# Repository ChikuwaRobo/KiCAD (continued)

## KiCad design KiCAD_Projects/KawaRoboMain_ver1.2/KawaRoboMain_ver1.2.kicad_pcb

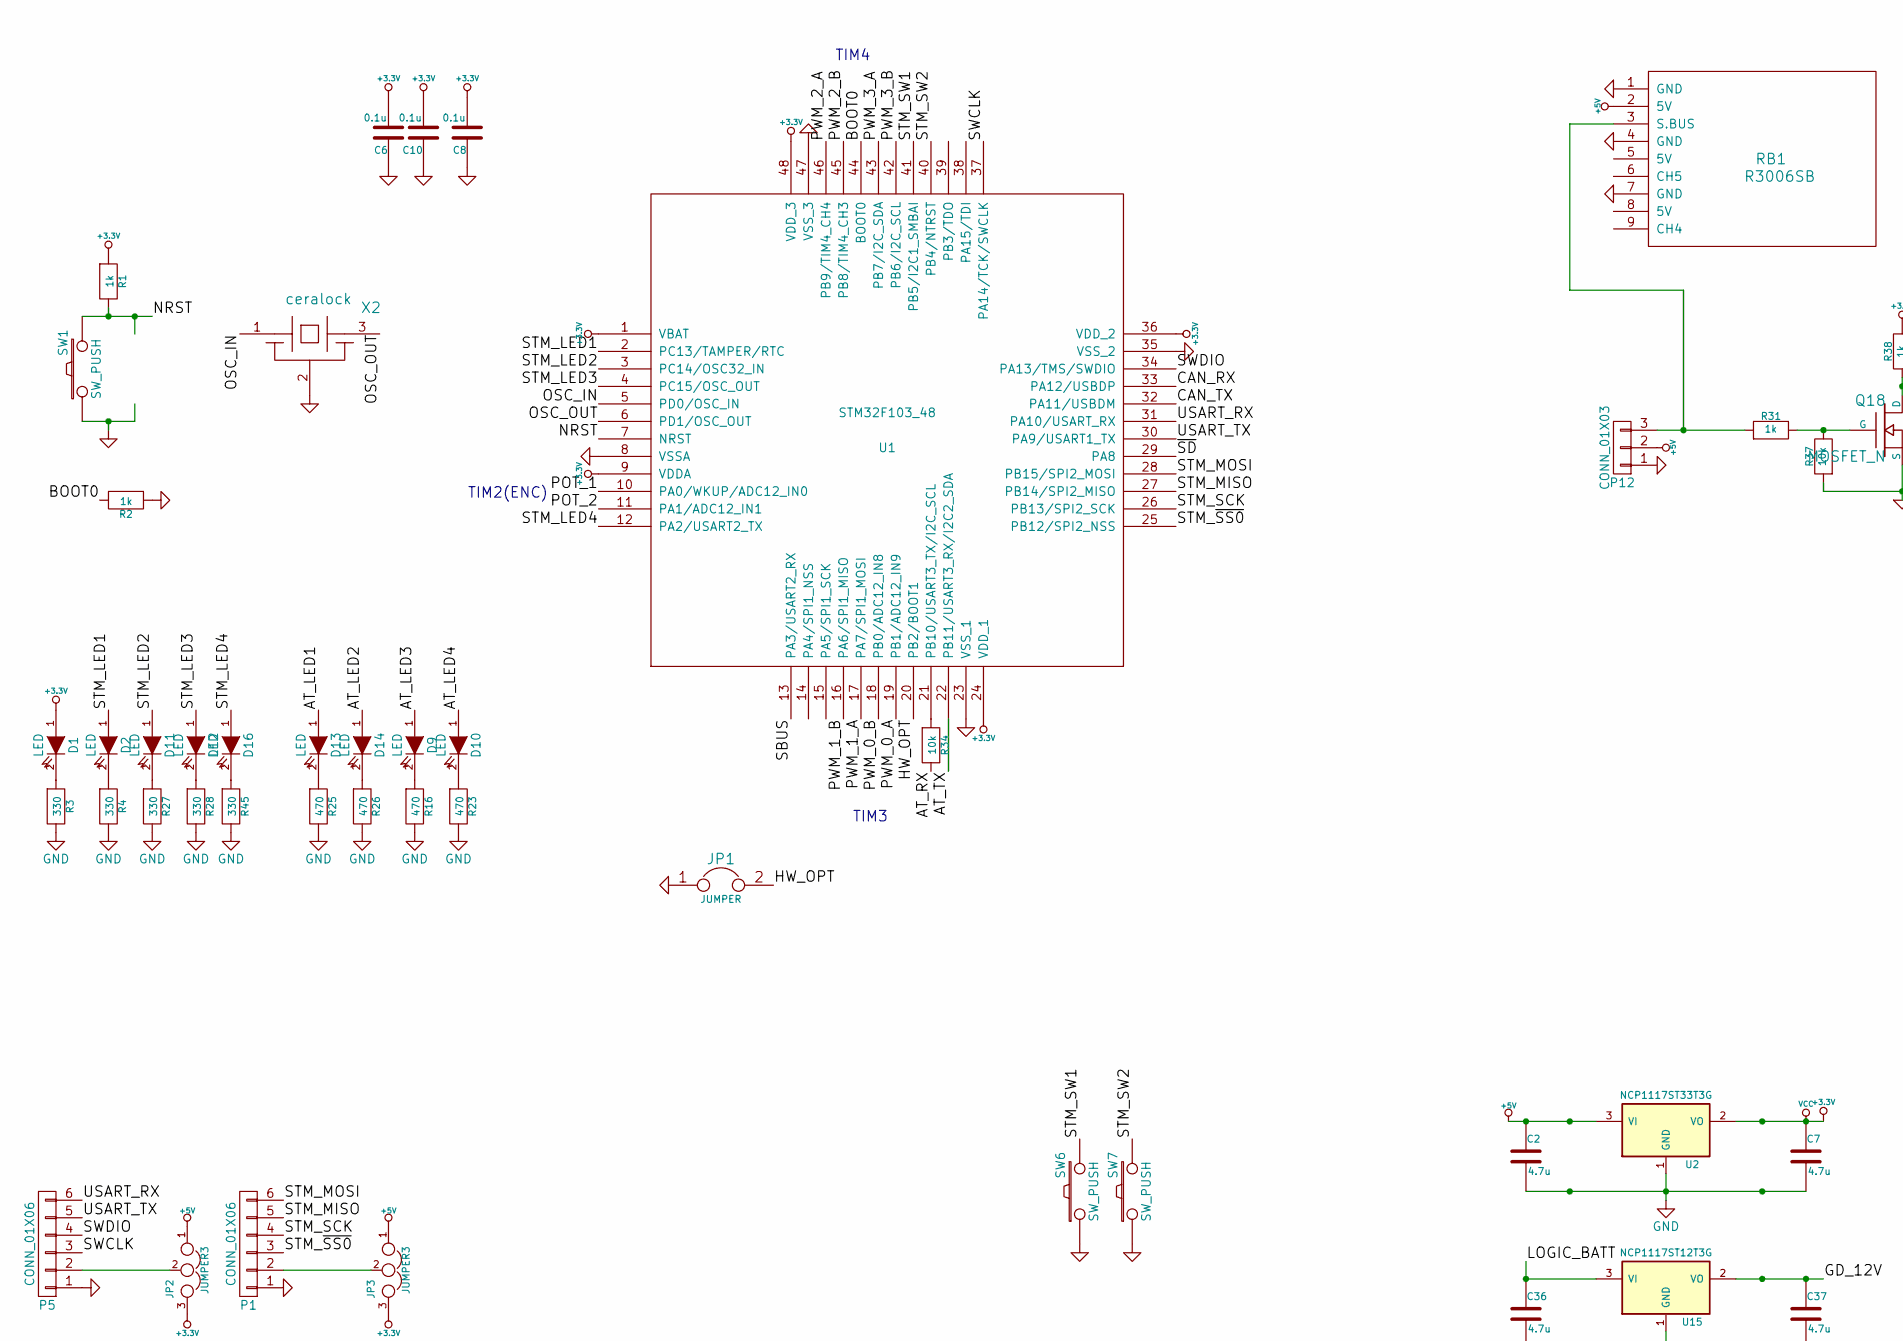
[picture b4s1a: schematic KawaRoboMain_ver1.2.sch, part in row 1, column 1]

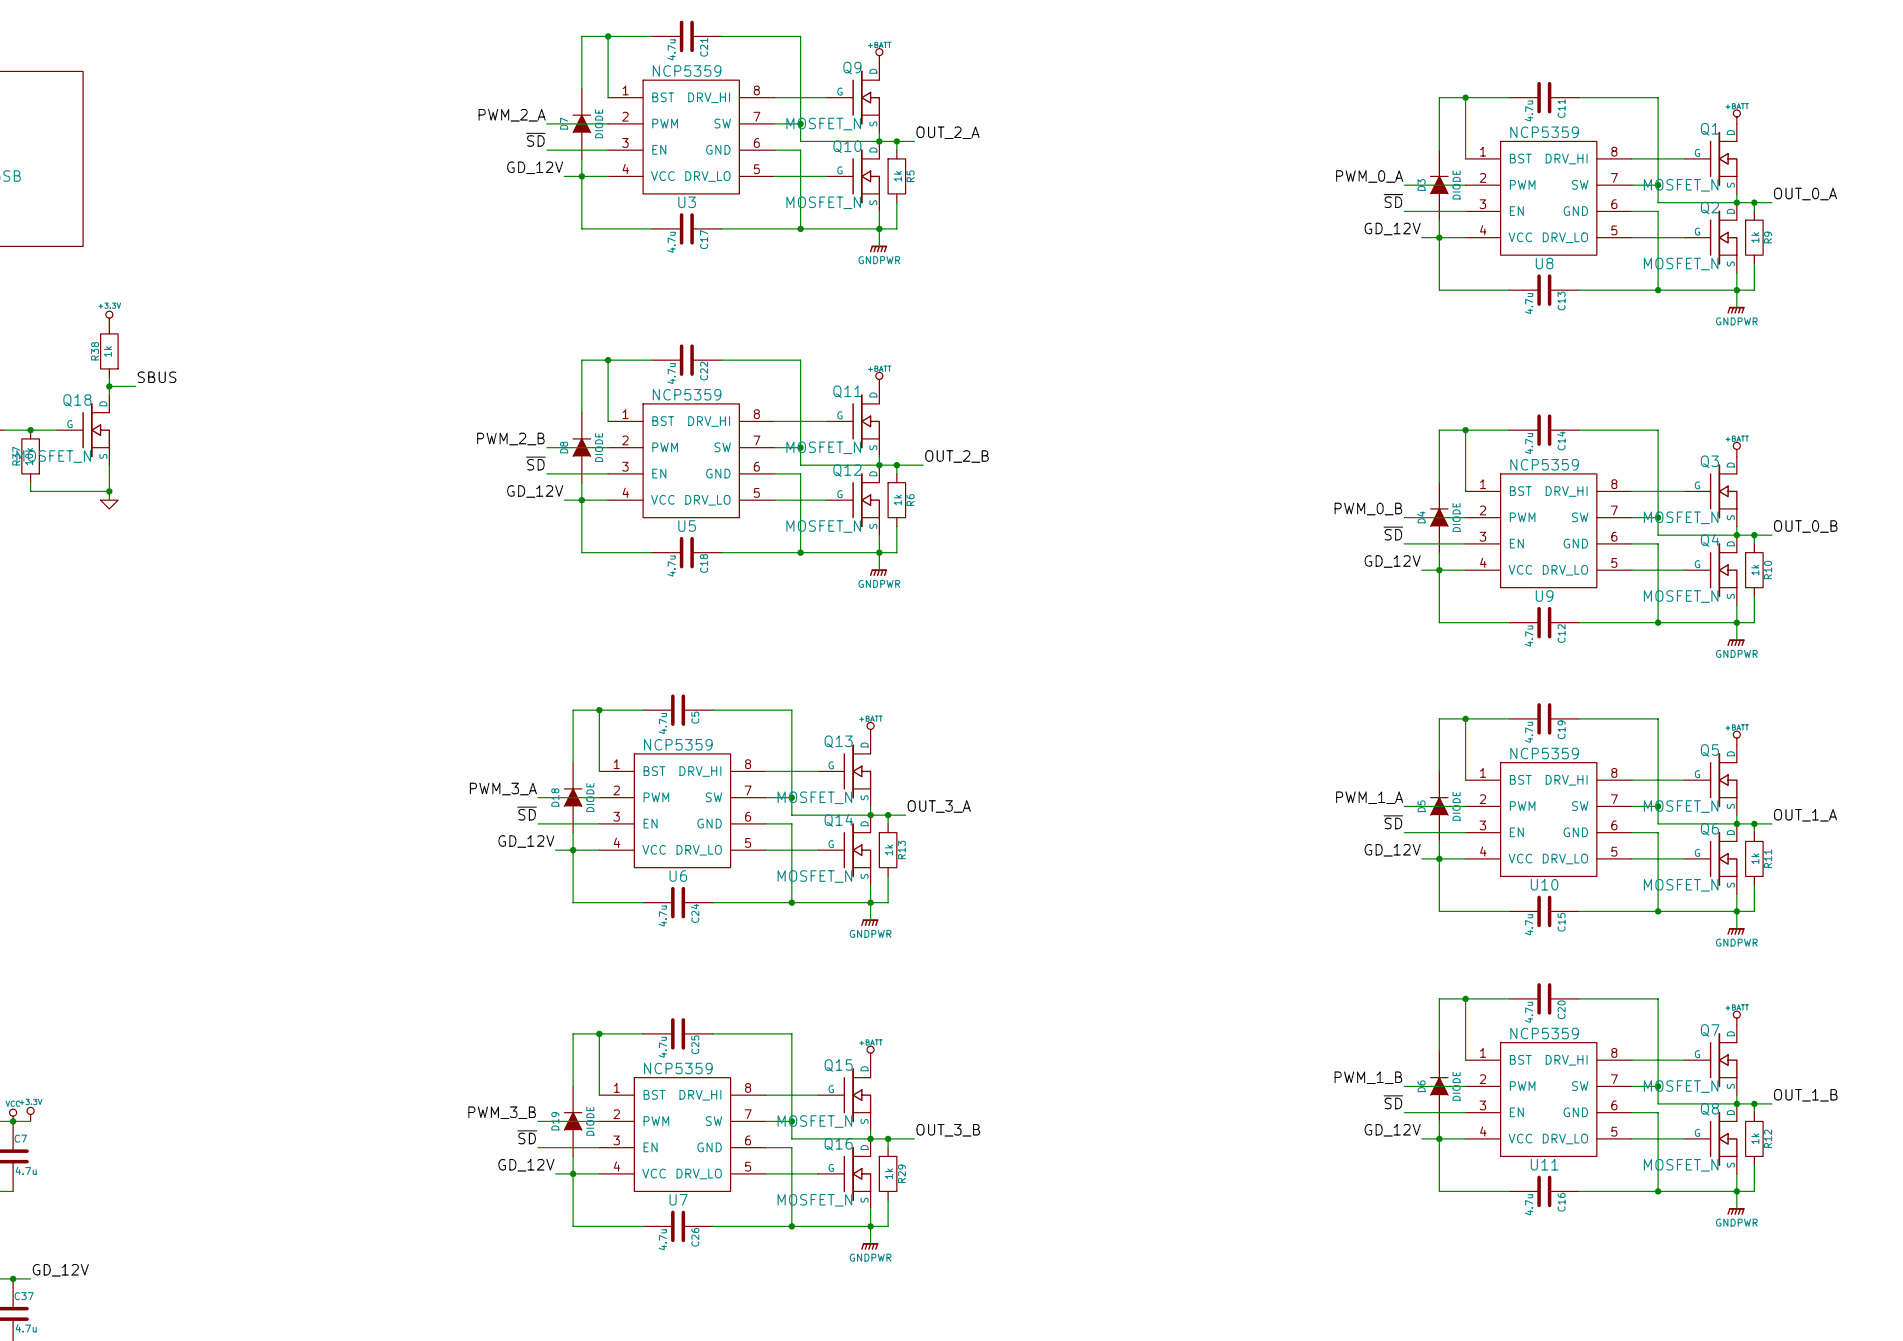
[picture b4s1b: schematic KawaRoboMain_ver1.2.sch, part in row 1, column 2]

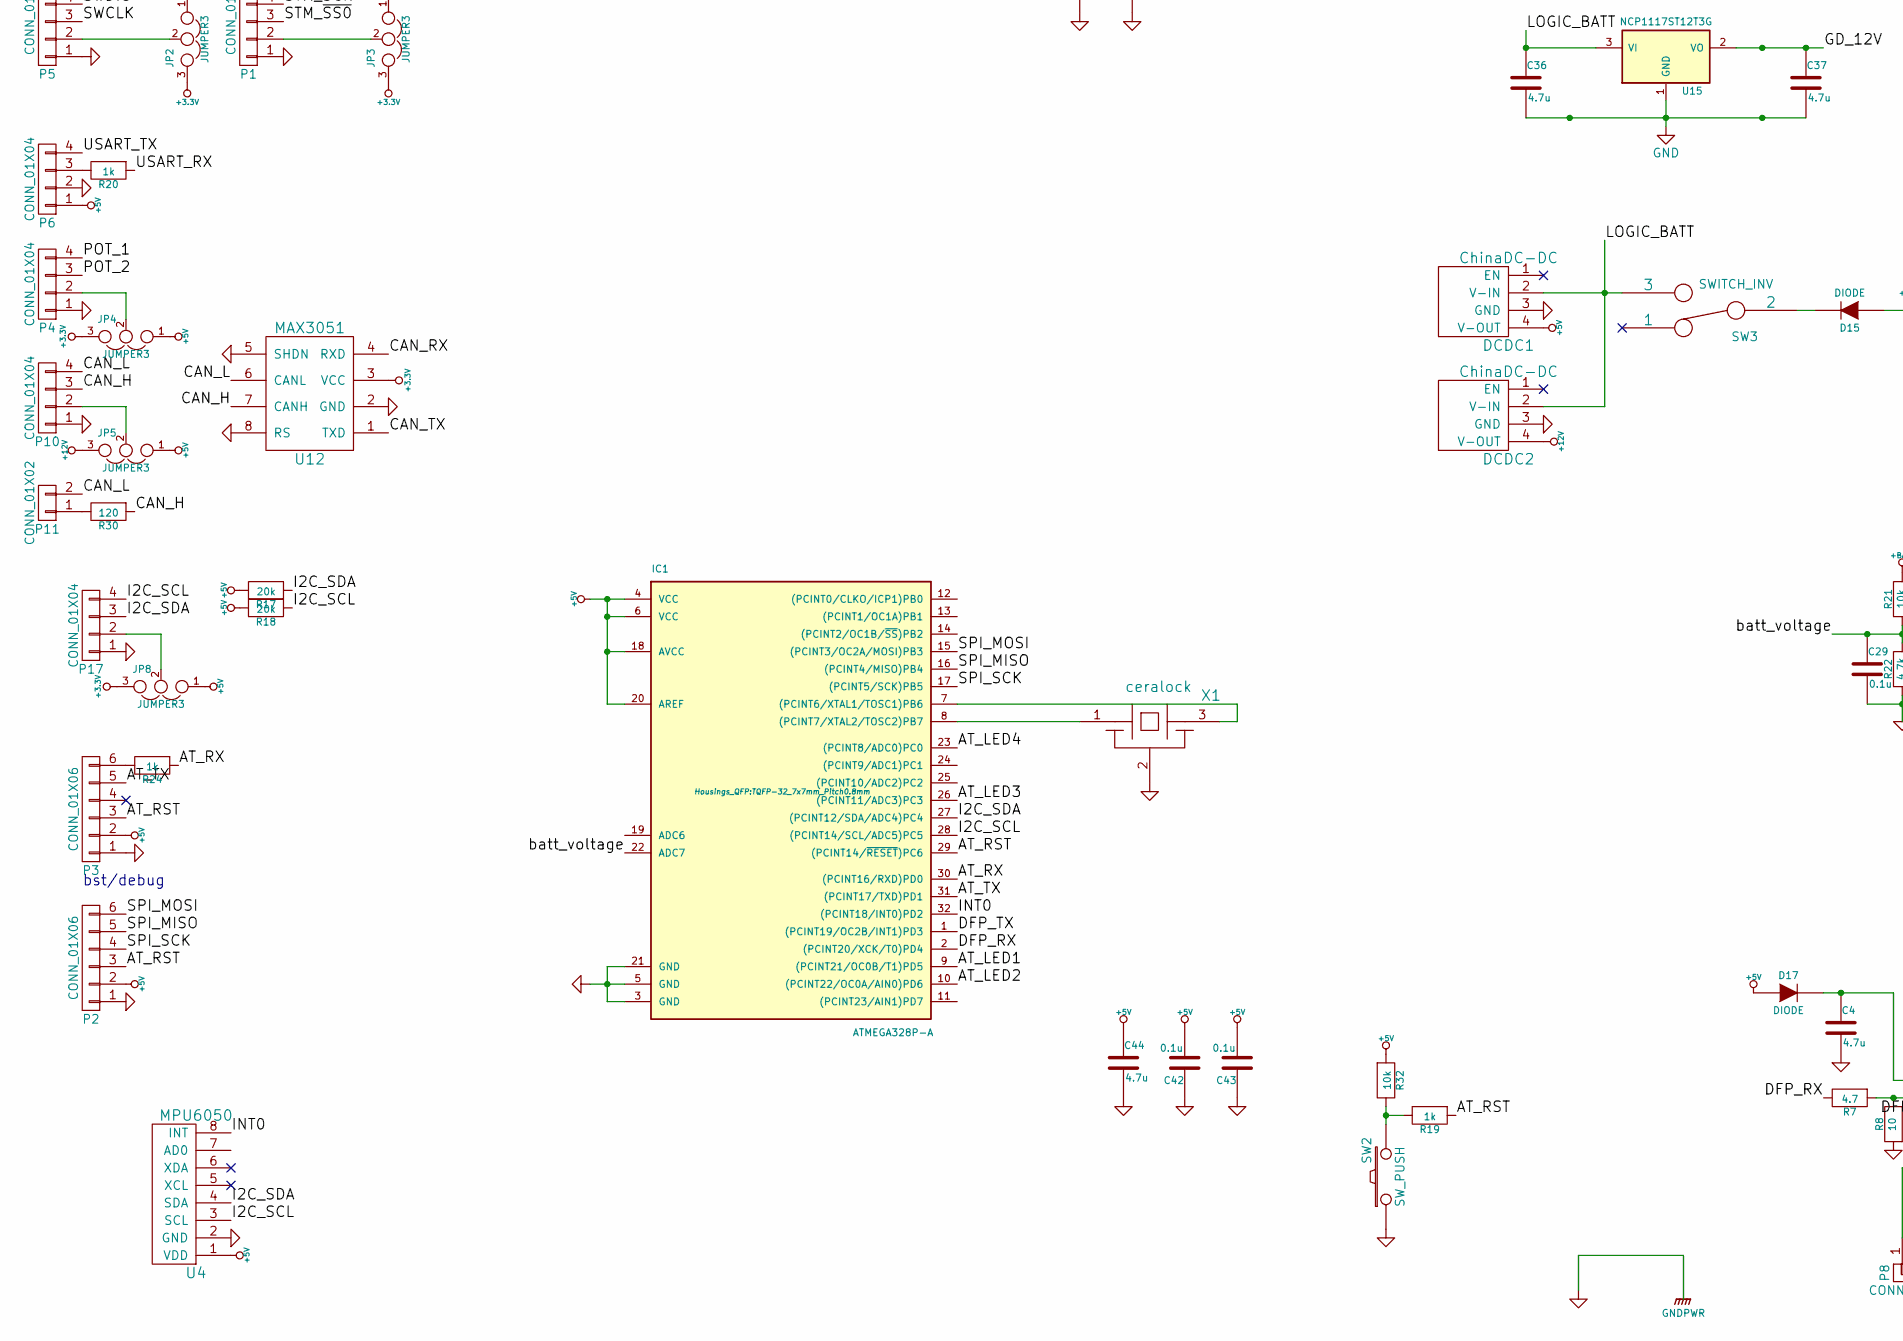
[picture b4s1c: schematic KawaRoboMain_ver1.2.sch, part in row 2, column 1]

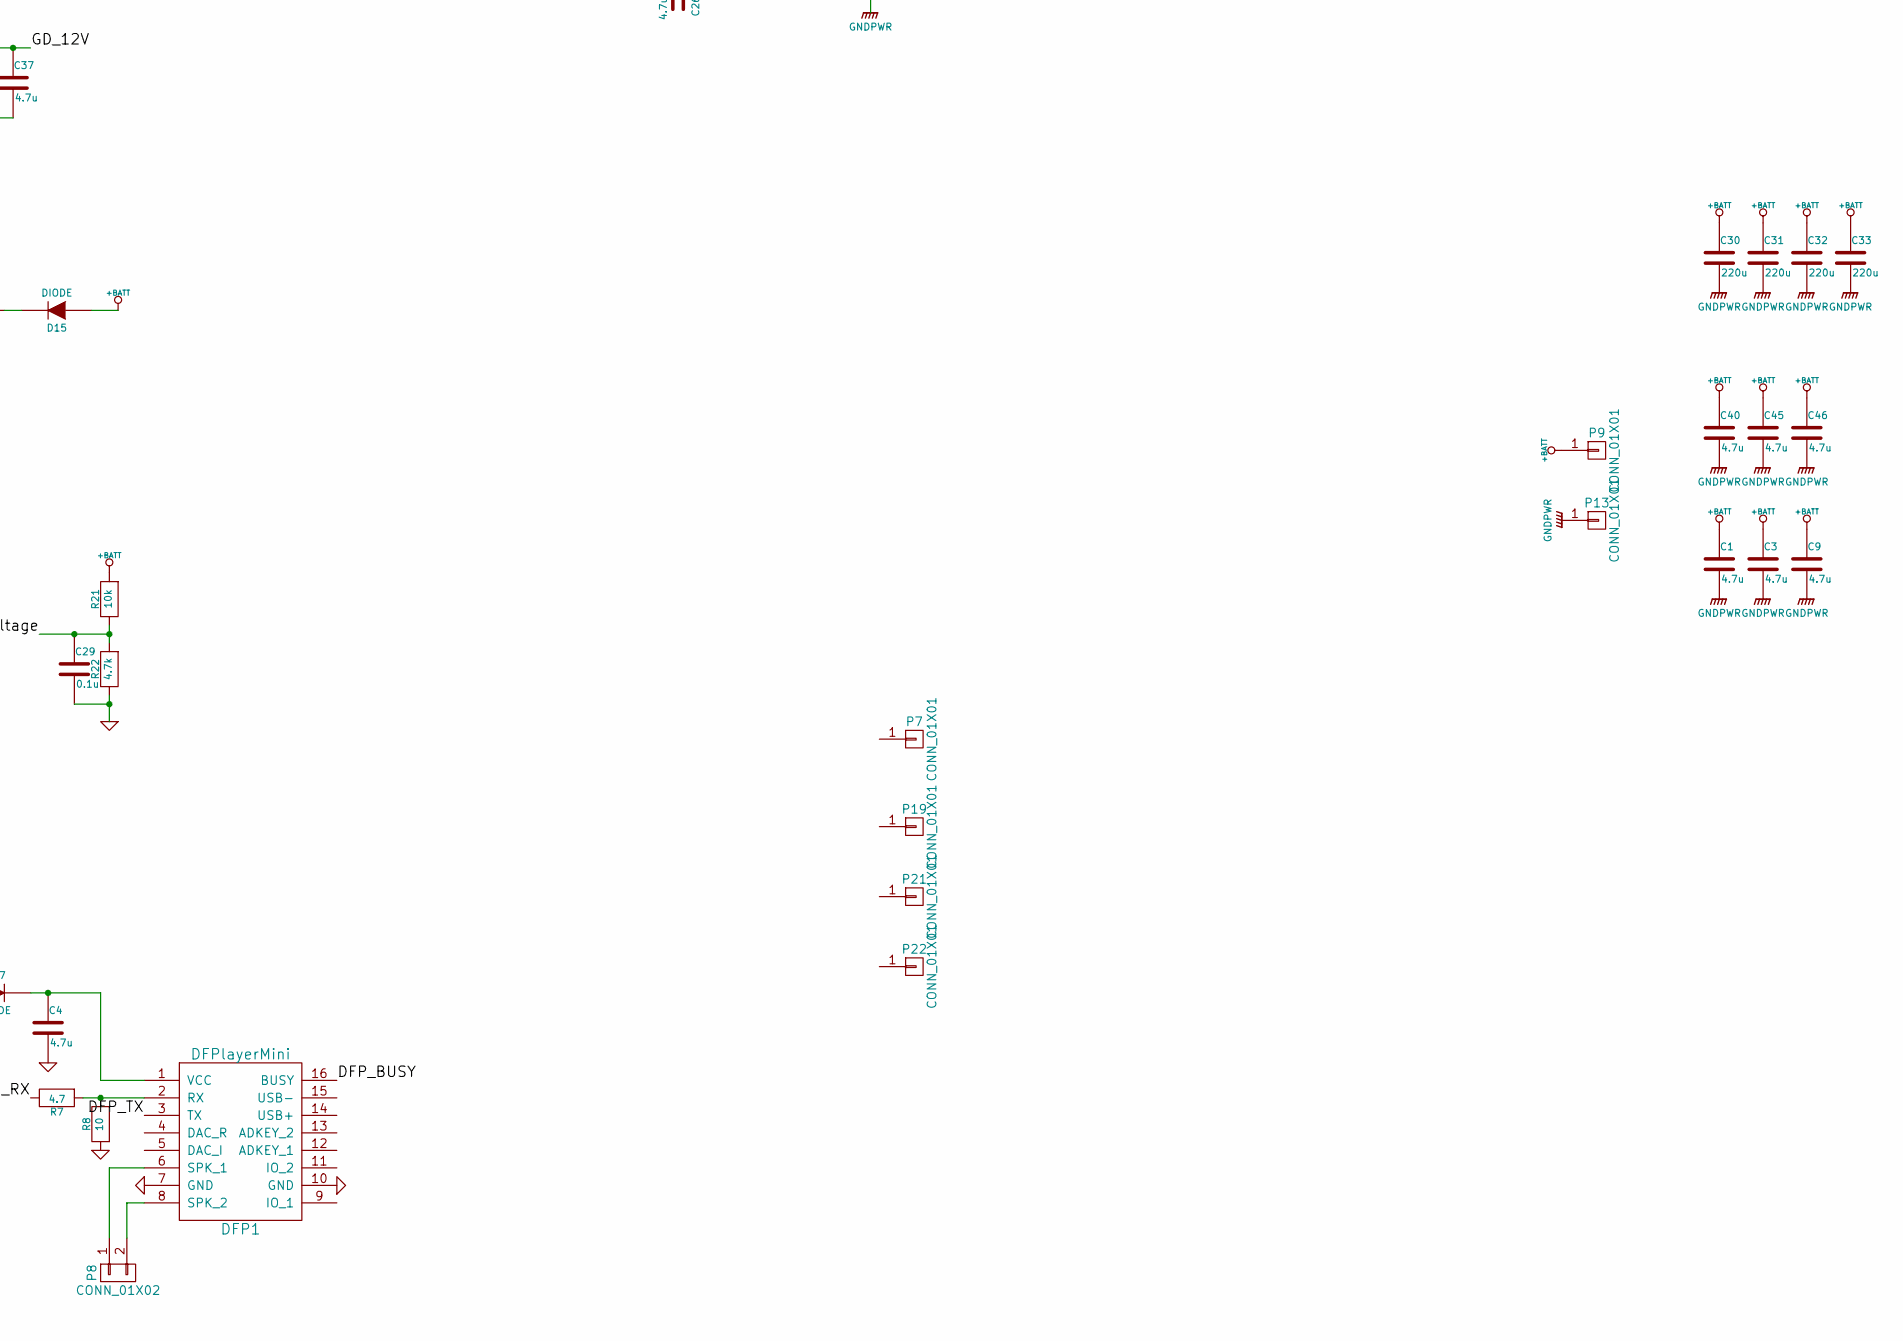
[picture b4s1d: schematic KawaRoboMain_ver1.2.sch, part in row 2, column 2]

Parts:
C1, C2, C3, C4, C5, C7, C9, C11, C12, C13, C14, C15, C16, C17, C18, C19, C20, C21, C22, C24, C25, C26, C36, C37, C40, C44, C45, C46: 4.7u; C3216_S
C6, C8, C10, C29, C42, C43: 0.1u; C1608_WP_S
C30, C31, C32, C33: 220u; C_Radial_D10_L13_P5
D1, D2, D9, D10, D11, D12, D13, D14, D16: LED; LED_0805
D3, D4, D5, D6, D7, D8, D18, D19: DIODE; C2012
D15, D17: DIODE; C3216_S
DCDC1, DCDC2: ChinaDC-DC
DFP1: DFPlayerMini; DFPlayer
IC1: ATMEGA328P-A; TQFP-32_7x7mm_Pitch0.8mm
JP1: JUMPER; GS2
JP2, JP3, JP4, JP5, JP8: JUMPER3; GS3
P1: CONN_01X06; XA_6T
P2, P3, P5: CONN_01X06; ZH_6T
P4, P10, P17: CONN_01X04; XA_4T
P6: CONN_01X04; Socket_Strip_Straight_1x04
P7: CONN_01X01; V_BattMeter
P8: CONN_01X02; XA_2T
P9, P13: CONN_01X01; 1pin
P11: CONN_01X02; Pin_Header_Straight_1x02
P12: CONN_01X03; XA_3T
P19: CONN_01X01; KawaRobo_Headsink
P21: CONN_01X01; kw
P22: CONN_01X01; ckw
Q1, Q2, Q3, Q4, Q5, Q6, Q7, Q8, Q9, Q10, Q11, Q12, Q13, Q14, Q15, Q16: MOSFET_N; SOT-428_GDS_compact
Q18: MOSFET_N; SOT-23_Handsoldering
R1, R2, R5, R6, R9, R10, R11, R12, R13, R19, R20, R24, R29, R31, R38: 1k; C1608_WP_S
R3, R4, R27, R28, R45: 330; C1608_WP_S
R7: 4.7; C1608_WP_S
R8: 10; C1608_WP_S
R16, R23, R25, R26: 470; C1608_WP_S
R17, R18: 20k; C1608_WP_S
R21, R32, R34, R37: 10k; C1608_WP_S
R22: 4.7k; C1608_WP_S
R30: 120; C1608_WP_S
RB1: R3006SB
SW1, SW2, SW6, SW7: SW_PUSH; RP_SMD_Button
SW3: SWITCH_INV; RSpro_SlideSide
U1: STM32F103_48; LQFP-48_7x7mm_Pitch0.5mm
U2: NCP1117ST33T3G; SOT-223_reg
U3, U5, U6, U7, U8, U9, U10, U11: NCP5359; SOIC-8_3.9x4.9mm_Pitch1.27mm_S
U4: MPU6050; MPU-6050
U12: MAX3051; SOIC-8_3.9x4.9mm_Pitch1.27mm_S
U15: NCP1117ST12T3G; SOT-223_reg
X1, X2: ceralock; Resonator_3×1.3mm

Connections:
+3.3V: C6.2, C7.1, C8.2, C10.2, D1.1 (A), JP2.3, JP3.3, JP4.3, JP8.3, R1.1, R38.2, U1.1 (VBAT), U1.9 (VDDA), U1.24 (VDD_1), U1.36 (VDD_2), U1.48 (VDD_3), U2.2 (VO), U12.3 (VCC)
+5V: C2.1, C42.2, C43.2, C44.1, D17.2 (A), DCDC1.4 (V-OUT), IC1.4 (VCC), IC1.6 (VCC), IC1.18 (AVCC), IC1.20 (AREF), JP2.1, JP3.1, JP4.1, JP5.1, JP8.1, P2.2, P3.2, P6.1, P12.2, R17.2, R18.2, R32.1, RB1.2 (5V), U2.3 (VI), U4.1 (VDD)
+12V: DCDC2.4 (V-OUT), JP5.3
+BATT: C1.1, C3.1, C9.1, C30.1, C31.1, C32.1, C33.1, C40.1, C45.1, C46.1, D15.2 (A), P9.1, Q1.D, Q3.D, Q5.D, Q7.D, Q9.D, Q11.D, Q13.D, Q15.D, R21.1
/AT_LED1: D13.1 (A), IC1.9 ((PCINT21/OC0B/T1)PD5)
/AT_LED2: D14.1 (A), IC1.10 ((PCINT22/OC0A/AIN0)PD6)
/AT_LED3: D9.1 (A), IC1.26 ((PCINT11/ADC3)PC3)
/AT_LED4: D10.1 (A), IC1.23 ((PCINT8/ADC0)PC0)
/AT_RST: IC1.29 ((PCINT14/~RESET~)PC6), P2.3, P3.3, R19.1
/AT_RX: IC1.30 ((PCINT16/RXD)PD0), R24.1, R34.2
/AT_TX: IC1.31 ((PCINT17/TXD)PD1), P3.5, U1.22 (PB11/USART3_RX/I2C2_SDA)
/BOOT0: R2.2, U1.44 (BOOT0)
/CAN_H: P10.3, R30.1, U12.7 (CANH)
/CAN_L: P10.4, P11.2, U12.6 (CANL)
/CAN_RX: U1.33 (PA12/USBDP), U12.4 (RXD)
/CAN_TX: U1.32 (PA11/USBDM), U12.1 (TXD)
/DFP_RX: IC1.2 ((PCINT20/XCK/T0)PD4), R7.2
/DFP_TX: DFP1.3 (TX), IC1.1 ((PCINT19/OC2B/INT1)PD3)
/GD_12V: C12.2, C13.2, C15.2, C16.2, C17.2, C18.2, C24.2, C26.2, C37.1, D3.2 (A), D4.2 (A), D5.2 (A), D6.2 (A), D7.2 (A), D8.2 (A), D18.2 (A), D19.2 (A), U3.4 (VCC), U5.4 (VCC), U6.4 (VCC), U7.4 (VCC), U8.4 (VCC), U9.4 (VCC), U10.4 (VCC), U11.4 (VCC), U15.2 (VO)
/HW_OPT: JP1.2, U1.20 (PB2/BOOT1)
/I2C_SCL: IC1.28 ((PCINT14/SCL/ADC5)PC5), P17.4, R18.1, U4.3 (SCL)
/I2C_SDA: IC1.27 ((PCINT12/SDA/ADC4)PC4), P17.3, R17.1, U4.4 (SDA)
/INT0: IC1.32 ((PCINT18/INT0)PD2), U4.8 (INT)
/LOGIC_BATT: C36.1, DCDC1.2 (V-IN), DCDC2.2 (V-IN), SW3.3, U15.3 (VI)
/NRST: R1.2, SW1.2, U1.7 (NRST)
/OSC_IN: U1.5 (PD0/OSC_IN), X2.1
/OSC_OUT: U1.6 (PD1/OSC_OUT), X2.3
/OUT_0_A: C11.1, Q1.S, Q2.D, R9.1, U8.7 (SW)
/OUT_0_B: C14.1, Q3.S, Q4.D, R10.1, U9.7 (SW)
/OUT_1_A: C19.1, Q5.S, Q6.D, R11.1, U10.7 (SW)
/OUT_1_B: C20.1, Q7.S, Q8.D, R12.1, U11.7 (SW)
/OUT_2_A: C21.1, Q9.S, Q10.D, R5.1, U3.7 (SW)
/OUT_2_B: C22.1, Q11.S, Q12.D, R6.1, U5.7 (SW)
/OUT_3_A: C5.1, Q13.S, Q14.D, R13.1, U6.7 (SW)
/OUT_3_B: C25.1, Q15.S, Q16.D, R29.1, U7.7 (SW)
/POT_1: P4.4, U1.10 (PA0/WKUP/ADC12_IN0)
/POT_2: P4.3, U1.11 (PA1/ADC12_IN1)
/PWM_0_A: U1.19 (PB1/ADC12_IN9), U8.2 (PWM)
/PWM_0_B: U1.18 (PB0/ADC12_IN8), U9.2 (PWM)
/PWM_1_A: U1.17 (PA7/SPI1_MOSI), U10.2 (PWM)
/PWM_1_B: U1.16 (PA6/SPI1_MISO), U11.2 (PWM)
/PWM_2_A: U1.46 (PB9/TIM4_CH4), U3.2 (PWM)
/PWM_2_B: U1.45 (PB8/TIM4_CH3), U5.2 (PWM)
/PWM_3_A: U1.43 (PB7/I2C_SDA), U6.2 (PWM)
/PWM_3_B: U1.42 (PB6/I2C_SCL), U7.2 (PWM)
/SBUS: Q18.D, R38.1, U1.13 (PA3/USART2_RX)
/SPI_MISO: IC1.16 ((PCINT4/MISO)PB4), P2.5
/SPI_MOSI: IC1.15 ((PCINT3/OC2A/MOSI)PB3), P2.6
/SPI_SCK: IC1.17 ((PCINT5/SCK)PB5), P2.4
/STM_LED1: D2.1 (A), U1.2 (PC13/TAMPER/RTC)
/STM_LED2: D11.1 (A), U1.3 (PC14/OSC32_IN)
/STM_LED3: D12.1 (A), U1.4 (PC15/OSC_OUT)
/STM_LED4: D16.1 (A), U1.12 (PA2/USART2_TX)
/STM_MISO: P1.5, U1.27 (PB14/SPI2_MISO)
/STM_MOSI: P1.6, U1.28 (PB15/SPI2_MOSI)
/STM_SCK: P1.4, U1.26 (PB13/SPI2_SCK)
/STM_SW1: SW6.2, U1.41 (PB5/I2C1_SMBAI)
/STM_SW2: SW7.2, U1.40 (PB4/NTRST)
/STM_~SS0: P1.3, U1.25 (PB12/SPI2_NSS)
/SWCLK: P5.3, U1.37 (PA14/TCK/SWCLK)
/SWDIO: P5.4, U1.34 (PA13/TMS/SWDIO)
/USART_RX: P5.6, R20.1, U1.31 (PA10/USART_RX)
/USART_TX: P5.5, P6.4, U1.30 (PA9/USART1_TX)
/batt_voltage: C29.1, IC1.22 (ADC7), R21.2, R22.1
/~SD: U1.29 (PA8), U3.3 (EN), U5.3 (EN), U6.3 (EN), U7.3 (EN), U8.3 (EN), U9.3 (EN), U10.3 (EN), U11.3 (EN)
GND: C1.2, C2.2, C3.2, C4.2, C6.1, C7.2, C8.1, C9.2, C10.1, C12.1, C13.1, C15.1, C16.1, C17.1, C18.1, C24.1, C26.1, C29.2, C30.2, C31.2, C32.2, C33.2, C36.2, C37.2, C40.2, C42.1, C43.1, C44.2, C45.2, C46.2, DCDC1.3 (GND), DCDC2.3 (GND), DFP1.7 (GND), DFP1.10 (GND), IC1.3 (GND), IC1.5 (GND), IC1.21 (GND), JP1.1, P1.1, P2.1, P3.1, P4.1, P5.1, P6.2, P10.1, P12.1, P13.1, P17.1, Q2.S, Q4.S, Q6.S, Q8.S, Q10.S, Q12.S, Q14.S, Q16.S, Q18.S, R2.1, R3.2, R4.2, R5.2, R6.2, R8.1, R9.2, R10.2, R11.2, R12.2, R13.2, R16.2, R22.2, R23.2, R25.2, R26.2, R27.2, R28.2, R29.2, R37.1, R45.2, RB1.1 (GND), RB1.4 (GND), RB1.7 (GND), SW1.1, SW2.1, SW6.1, SW7.1, U1.8 (VSSA), U1.23 (VSS_1), U1.35 (VSS_2), U1.47 (VSS_3), U2.1 (GND), U3.6 (GND), U4.2 (GND), U5.6 (GND), U6.6 (GND), U7.6 (GND), U8.6 (GND), U9.6 (GND), U10.6 (GND), U11.6 (GND), U12.2 (GND), U12.5 (SHDN), U12.8 (RS), U15.1 (GND), X1.2, X2.2
unnamed: C4.1, D17.1 (K), DFP1.1 (VCC)
unnamed: C5.2, D18.1 (K), U6.1 (BST)
unnamed: C11.2, D3.1 (K), U8.1 (BST)
unnamed: C14.2, D4.1 (K), U9.1 (BST)
unnamed: C19.2, D5.1 (K), U10.1 (BST)
unnamed: C20.2, D6.1 (K), U11.1 (BST)
unnamed: C21.2, D7.1 (K), U3.1 (BST)
unnamed: C22.2, D8.1 (K), U5.1 (BST)
unnamed: C25.2, D19.1 (K), U7.1 (BST)
unnamed: D1.2 (K), R3.1
unnamed: D2.2 (K), R4.1
unnamed: D9.2 (K), R16.1
unnamed: D10.2 (K), R23.1
unnamed: D11.2 (K), R27.1
unnamed: D12.2 (K), R28.1
unnamed: D13.2 (K), R25.1
unnamed: D14.2 (K), R26.1
unnamed: D15.1 (K), SW3.2
unnamed: D16.2 (K), R45.1
unnamed: DFP1.2 (RX), R7.1, R8.2
unnamed: DFP1.6 (SPK_1), P8.1
unnamed: DFP1.8 (SPK_2), P8.2
unnamed: IC1.7 ((PCINT6/XTAL1/TOSC1)PB6), X1.3
unnamed: IC1.8 ((PCINT7/XTAL2/TOSC2)PB7), X1.1
unnamed: JP2.2, P5.2
unnamed: JP3.2, P1.2
unnamed: JP4.2, P4.2
unnamed: JP5.2, P10.2
unnamed: JP8.2, P17.2
unnamed: P3.6, R24.2
unnamed: P6.3, R20.2
unnamed: P11.1, R30.2
unnamed: P12.3, R31.1, RB1.3 (S.BUS)
unnamed: Q1.G, U8.8 (DRV_HI)
unnamed: Q2.G, U8.5 (DRV_LO)
unnamed: Q3.G, U9.8 (DRV_HI)
unnamed: Q4.G, U9.5 (DRV_LO)
unnamed: Q5.G, U10.8 (DRV_HI)
unnamed: Q6.G, U10.5 (DRV_LO)
unnamed: Q7.G, U11.8 (DRV_HI)
unnamed: Q8.G, U11.5 (DRV_LO)
unnamed: Q9.G, U3.8 (DRV_HI)
unnamed: Q10.G, U3.5 (DRV_LO)
unnamed: Q11.G, U5.8 (DRV_HI)
unnamed: Q12.G, U5.5 (DRV_LO)
unnamed: Q13.G, U6.8 (DRV_HI)
unnamed: Q14.G, U6.5 (DRV_LO)
unnamed: Q15.G, U7.8 (DRV_HI)
unnamed: Q16.G, U7.5 (DRV_LO)
unnamed: Q18.G, R31.2, R37.2
unnamed: R19.2, R32.2, SW2.2
unnamed: R34.1, U1.21 (PB10/USART3_TX/I2C_SCL)

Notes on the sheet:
bst/debug
TIM3
TIM4
TIM2(ENC)

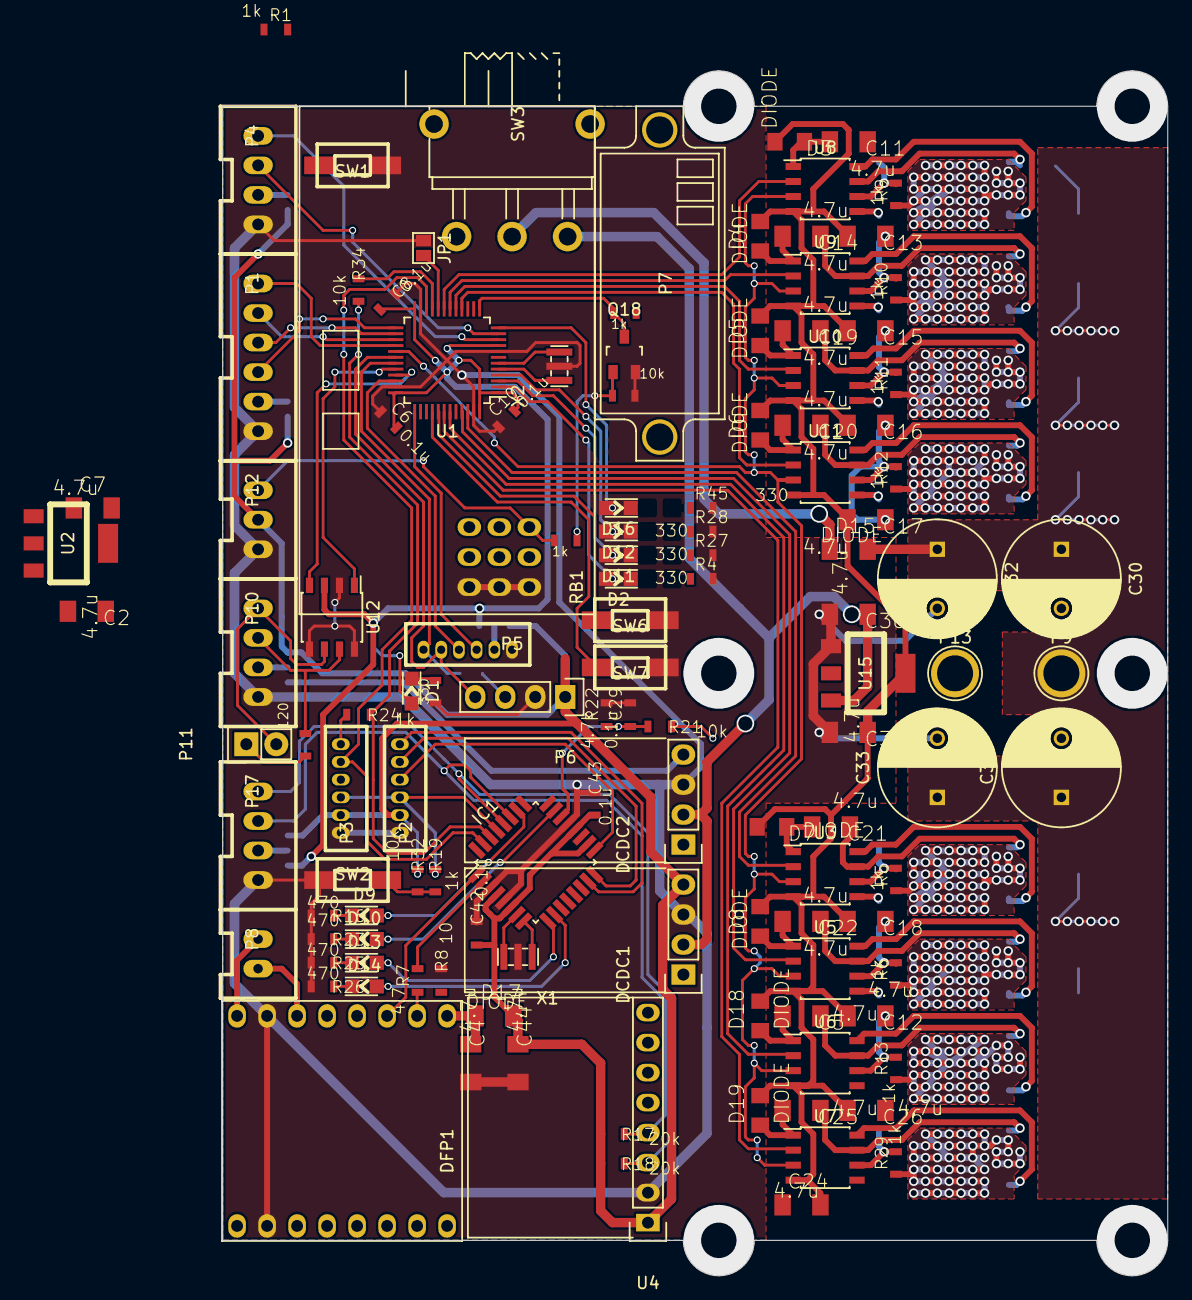
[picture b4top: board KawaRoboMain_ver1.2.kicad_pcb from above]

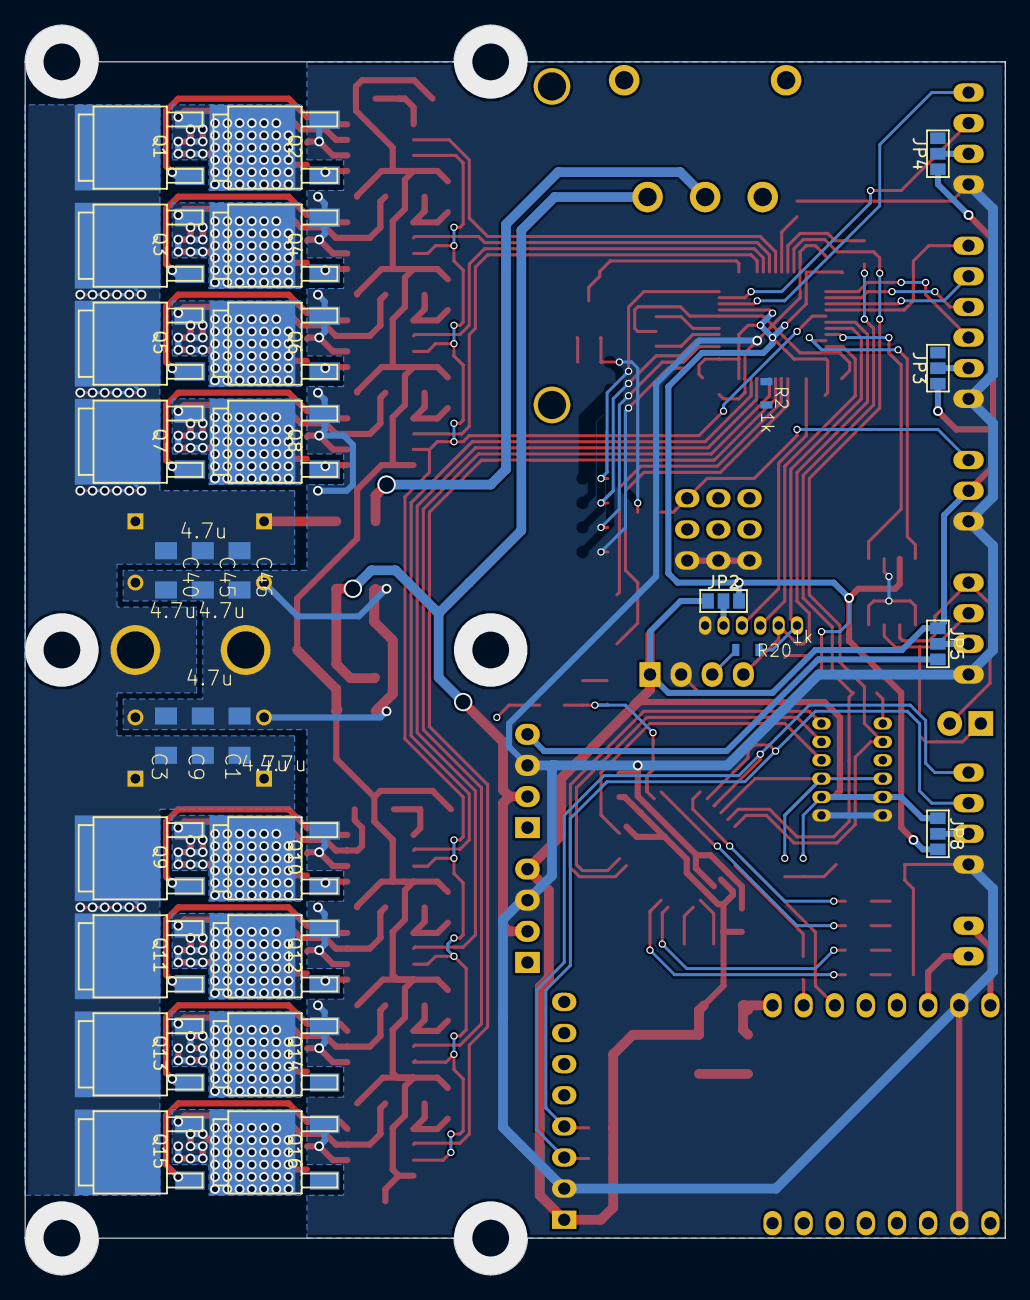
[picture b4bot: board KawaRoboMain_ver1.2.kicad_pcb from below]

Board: 2 copper layers, 80.0 x 102.0 mm, 156 parts (30 on the bottom side), 118 nets.
